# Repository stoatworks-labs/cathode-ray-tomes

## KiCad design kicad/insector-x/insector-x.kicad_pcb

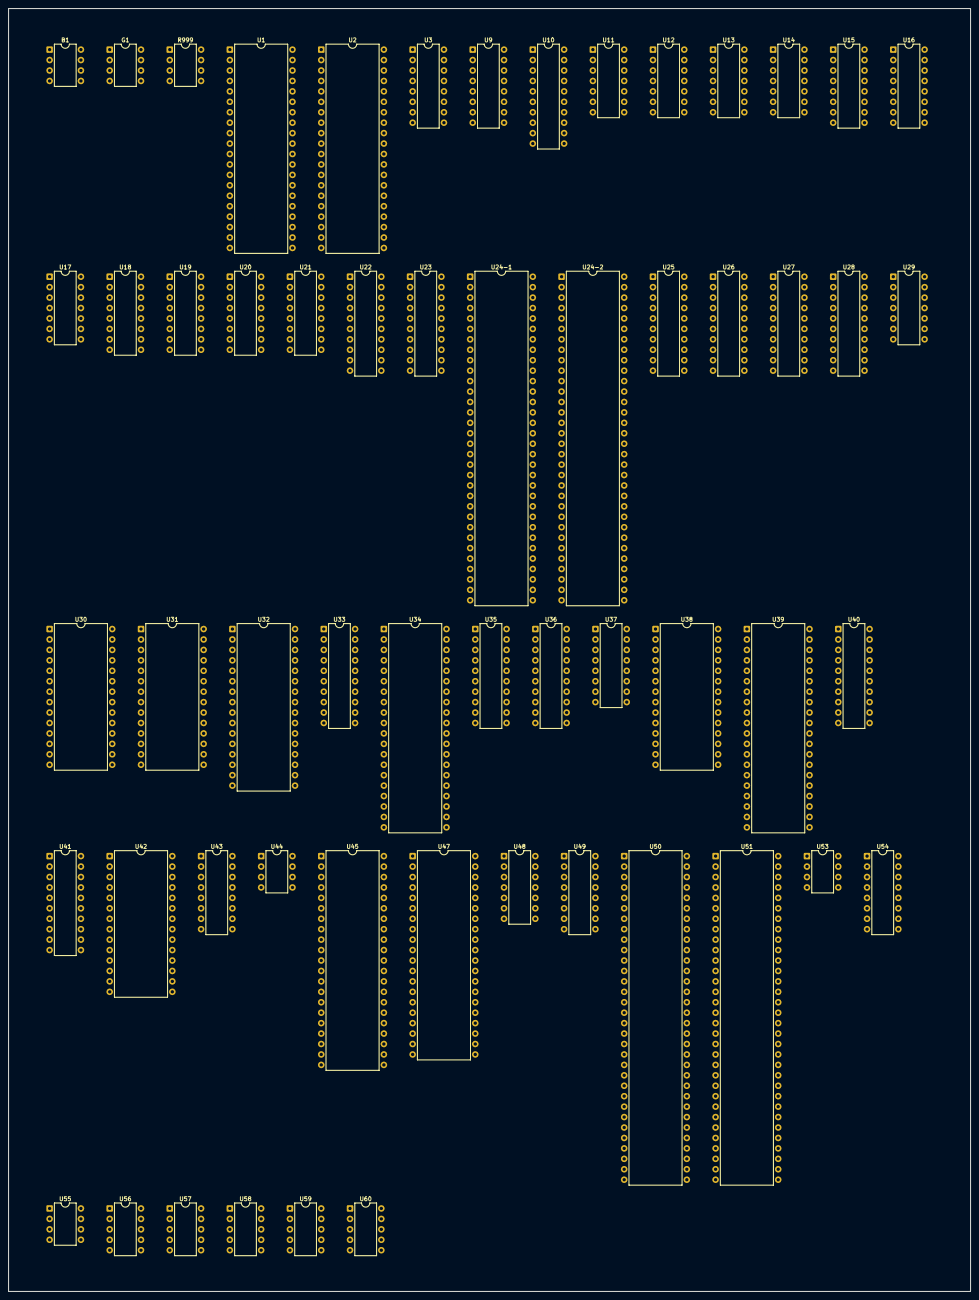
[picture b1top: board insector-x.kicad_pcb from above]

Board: 2 copper layers, 234.1 x 312.2 mm, 57 parts (0 on the bottom side), 330 nets, no tracks yet.

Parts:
B1: R0-012; DIP-8_W7.62mm
G1: R0-012; DIP-8_W7.62mm
R999: R0-012; DIP-8_W7.62mm
U1, U2: LH53400; DIP-40_W15.24mm
U3: 74LS139; DIP-16_W7.62mm
U9, U15, U37: 74LS174; DIP-16_W7.62mm
U10, U41: 74LS374; DIP-20_W7.62mm
U11: 74LS04; DIP-14_W7.62mm
U12: 74LS08; DIP-14_W7.62mm
U13, U14, U17: 74LS74; DIP-14_W7.62mm
U16, U18, U19, U20, U21: 74LS157; DIP-16_W7.62mm
U22: 74LS244_Split; DIP-20_W7.62mm
U23, U27, U28, U33, U40: 74LS245; DIP-20_W7.62mm
U24-1: YM3906; DIP-64_W15.24mm
U24-2: YM3909; DIP-64_W15.24mm
U25, U26, U35, U36: PAL16L8; DIP-20_W7.62mm
U29: 74LS32; DIP-14_W7.62mm
U30: HM6264; DIP-28_W15.24mm
U31: uPD43256BCZ-B; DIP-28_W15.24mm
U32: 27C010; DIP-32_W15.24mm
U34, U39: Z80CPU; DIP-40_W15.24mm
U38: 27512; DIP-28_W15.24mm
U42: TMM2063AP_10; DIP-28_W15.24mm
U43: TD62064; DIP-16_W7.62mm
U44: NJM4558; DIP-8_W7.62mm
U45: X1-007; DIP-42_W15.24mm
U47: YM2203; DIP-40_W15.24mm
U48: 74LS14; DIP-14_W7.62mm
U49, U54: 74LS161; DIP-16_W7.62mm
U50: X1-006; DIP-64_W15.24mm
U51: X1-004; DIP-64_W15.24mm
U53: YM3014; DIP-8_W7.62mm
U55: MB3730; DIP-8_W7.62mm
U56, U57, U58, U59, U60: X2-005; DIP-10_W7.62mm

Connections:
+12V: U43.1, U43.8, U55.7
/CPU/CNT_UP1: U37.5, U51.33
/CPU/CNT_UP2: U37.2, U51.32
/CPU/H2B: U12.4, U17.2, U22.18, U29.10, U47.38
/CPU/H4B: U12.5, U22.12, U23.19, U29.13, U33.19, U35.11
/CPU/MA0: U21.10, U23.8, U31.10, U32.12, U39.30, U50.34
/CPU/MA1: U21.13, U23.9, U31.9, U32.11, U39.31, U50.43
/CPU/MA2: U19.3, U23.7, U31.8, U32.10, U39.32, U50.42
/CPU/MA3: U20.13, U23.2, U31.7, U32.9, U39.33, U50.41
/CPU/MA4: U21.3, U23.4, U31.6, U32.8, U39.34, U50.40
/CPU/MA5: U21.6, U23.6, U31.5, U32.7, U39.35, U50.39
/CPU/MA6: U20.10, U31.4, U32.6, U33.4, U39.36, U50.38
/CPU/MA7: U20.6, U31.3, U32.5, U33.6, U39.37, U50.37
/CPU/MA8: U18.3, U31.25, U32.27, U33.7, U39.38, U50.36
/CPU/MA9: U18.6, U31.24, U32.26, U33.5, U36.7, U39.39, U50.35
/CPU/MA10: U19.10, U31.21, U32.23, U33.3, U36.6, U39.40
/CPU/MA11: U20.3, U24-1.27, U31.23, U32.25, U33.2, U36.5, U39.1
/CPU/MA12: U16.2, U19.13, U31.2, U32.4, U36.4, U39.2
/CPU/MA13: U31.1, U32.28, U36.3, U39.3
/CPU/MA14: U35.2, U36.2, U39.4
/CPU/MA15: U35.1, U36.1, U39.5
/CPU/MBSWD0: U15.2, U31.26, U35.7
/CPU/MBSWD1: U15.5, U35.6
/CPU/MBSWD2: U15.7, U35.5
/CPU/MCK6M: U14.11, U22.3, U22.15, U39.6
/CPU/MD0: U15.3, U28.9, U31.11, U32.13, U39.14, U40.3, U50.48, U50.56
/CPU/MD1: U15.4, U28.8, U31.12, U32.14, U39.15, U40.2, U50.49, U50.57
/CPU/MD2: U15.6, U28.7, U31.13, U32.15, U39.12, U40.9, U50.50, U50.58
/CPU/MD3: U15.14, U28.6, U31.15, U32.17, U39.8, U40.8, U50.51, U50.59
/CPU/MD4: U15.13, U28.5, U31.16, U32.18, U39.7, U40.7, U50.52, U50.60
/CPU/MD5: U15.11, U28.4, U31.17, U32.19, U39.9, U40.6, U50.53, U50.61
/CPU/MD6: U28.3, U31.18, U32.20, U39.10, U40.5, U50.54, U50.62
/CPU/MD7: U28.2, U31.19, U32.21, U39.13, U40.4, U50.55, U50.63
/CPU/MRA14: U32.29, U35.14
/CPU/MRA15: U32.3, U35.13
/CPU/MRA16: U32.2, U35.12
/CPU/SA0: U21.11, U34.30, U38.10, U47.37, U51.37
/CPU/SA1: U3.2, U21.14, U34.31, U38.9
/CPU/SA2: U3.3, U19.2, U34.32, U38.8
/CPU/SA3: U20.14, U34.33, U38.7
/CPU/SA4: U21.2, U34.34, U38.6
/CPU/SA5: U21.5, U34.35, U38.5
/CPU/SA6: U20.11, U34.36, U38.4
/CPU/SA7: U20.5, U34.37, U38.3
/CPU/SA8: U18.2, U34.38, U38.25
/CPU/SA9: U18.5, U34.39, U38.24
/CPU/SA10: U19.11, U34.40, U38.21
/CPU/SA11: U20.2, U25.5, U34.1, U38.23
/CPU/SA12: U19.14, U25.4, U34.2, U38.2
/CPU/SA13: U25.3, U34.3
/CPU/SA14: U25.2, U34.4
/CPU/SA15: U25.1, U34.5, U38.1
/CPU/SBANK0: U25.11, U37.15
/CPU/SBANK1: U25.9, U37.12
/CPU/SCK6M: U13.3, U13.11, U22.5, U34.6
/CPU/SD0: U27.9, U34.14, U37.14, U38.11, U47.40, U51.28, U51.44
/CPU/SD1: U27.8, U34.15, U37.13, U38.12, U47.2, U51.29, U51.45
/CPU/SD2: U27.7, U34.12, U37.11, U38.13, U47.3, U51.30, U51.46
/CPU/SD3: U27.6, U34.8, U37.6, U38.15, U47.4, U51.31, U51.47
/CPU/SD4: U27.5, U34.7, U37.4, U38.16, U47.5, U51.48
/CPU/SD5: U27.4, U34.9, U37.3, U38.17, U47.6, U51.49
/CPU/SD6: U27.3, U34.10, U38.18, U47.7, U51.50
/CPU/SD7: U27.2, U34.13, U38.19, U47.8, U51.51
/CPU/SET_LOCK1: U37.10, U51.35
/CPU/SET_LOCK2: U37.7, U51.34
/CPU/SHA0: U21.9, U30.10
/CPU/SHA1: U21.12, U30.9
/CPU/SHA2: U19.4, U30.8
/CPU/SHA3: U20.12, U30.7
/CPU/SHA4: U21.4, U30.6
/CPU/SHA5: U21.7, U30.5
/CPU/SHA6: U20.9, U30.4
/CPU/SHA7: U20.7, U30.3
/CPU/SHA8: U18.4, U30.25
/CPU/SHA9: U18.7, U30.24
/CPU/SHA10: U19.9, U30.21
/CPU/SHA11: U20.4, U30.23
/CPU/SHA12: U19.12, U30.2
/CPU/SHD0: U27.11, U28.11, U30.19
/CPU/SHD1: U27.12, U28.12, U30.18
/CPU/SHD2: U27.13, U28.13, U30.17
/CPU/SHD3: U27.14, U28.14, U30.16
/CPU/SHD4: U27.15, U28.15, U30.15
/CPU/SHD5: U27.16, U28.16, U30.13
/CPU/SHD6: U27.17, U28.17, U30.12
/CPU/SHD7: U27.18, U28.18, U30.11
/CPU/SRA13: U25.18, U38.26
/CPU/SRA14: U25.19, U38.27
/CPU/~BGTRNSP: U24-2.2, U36.14
/CPU/~BNKSW: U15.9, U36.15
/CPU/~MIORQ: U14.1, U39.20
/CPU/~MMREQ: U35.3, U36.8, U39.19
/CPU/~MRAMCS: U31.20, U35.16
/CPU/~MRD: U11.9, U18.10, U24-1.2, U28.1, U31.22, U39.21, U40.1, U50.44
/CPU/~MRFSH: U35.4, U36.9, U39.28
/CPU/~MROMCS: U32.24, U35.15
/CPU/~MSHRAMEN: U26.16, U28.19
/CPU/~MSHRAMRQ: U26.1, U36.18
/CPU/~MWAIT: U26.14, U39.24
/CPU/~MWR: U26.2, U31.27, U36.11, U39.22, U50.47
/CPU/~OBJCODEHI: U35.9, U36.17
/CPU/~OBJCODELO: U35.8, U36.16
/CPU/~OBJORVRAMEN: U26.5, U29.12, U36.19
/CPU/~OBJRAMCS: U35.19, U42.20
/CPU/~PALEN: U36.12, U50.45
/CPU/~RDINPUTS: U3.1, U25.16
/CPU/~SBNKSW: U25.14, U37.9
/CPU/~SHRAMCS: U26.17, U30.20
/CPU/~SHRAMRD: U18.9, U30.22
/CPU/~SHRAMWR: U26.18, U30.27
/CPU/~SIORQ: U17.13, U34.20
/CPU/~SMREQ: U25.7, U34.19
/CPU/~SRD: U18.11, U27.1, U34.21, U47.36
/CPU/~SRFSH: U25.8, U34.28
/CPU/~SROMCS: U25.12, U38.22
/CPU/~SRST: U12.3, U34.26, U37.1, U47.24
/CPU/~SSHRAMENB: U18.1, U19.1, U20.1, U21.1, U26.19
/CPU/~SSHRAMEN: U26.15, U27.19
/CPU/~SSHRAMRQ: U25.13, U26.3
/CPU/~SWAIT: U26.13, U34.24
/CPU/~SWR: U25.6, U26.4, U34.22, U47.35
/CPU/~VRAMWR: U24-1.3, U36.13
/CPU/~WDRES: U12.1, U15.1, U24-1.29, U39.26, U48.2, U48.4
/CPU/~YM2203CS: U13.2, U25.15, U47.34
/CPU/~YMIRQ: U34.17, U47.25
/Graphics/12M: U24-1.62, U24-2.3
/Graphics/B1: B1.3, U45.2
/Graphics/B2: B1.4, U45.3
/Graphics/B3: B1.5, U45.4
/Graphics/B4: B1.6, U45.5
/Graphics/B5: B1.7, U45.6
/Graphics/Bb: B1.2, U45.1
/Graphics/G1: G1.3, U45.8
/Graphics/G2: G1.4, U45.9
/Graphics/G2D0: U2.13, U24-2.56
/Graphics/G2D1: U2.15, U24-2.57
/Graphics/G2D2: U2.17, U24-2.58
/Graphics/G2D3: U2.19, U24-2.59
/Graphics/G2D4: U2.22, U24-2.60
/Graphics/G2D5: U2.24, U24-2.61
/Graphics/G2D6: U2.26, U24-2.62
/Graphics/G2D7: U2.28, U24-2.63
/Graphics/G2D8: U2.14, U24-2.48
/Graphics/G2D9: U2.16, U24-2.49
/Graphics/G2D10: U2.18, U24-2.50
/Graphics/G2D11: U2.20, U24-2.51
/Graphics/G2D12: U2.23, U24-2.52
/Graphics/G2D13: U2.25, U24-2.53
/Graphics/G2D14: U2.27, U24-2.54
/Graphics/G2D15: U2.29, U24-2.55
/Graphics/G3: G1.5, U45.11
/Graphics/G4: G1.6, U45.12
/Graphics/G5: G1.7, U45.13
/Graphics/GA0: U1.9, U2.9, U24-1.38
/Graphics/GA1: U1.8, U2.8, U24-1.37
/Graphics/GA2: U1.7, U2.7, U24-1.36
/Graphics/GA4: U1.5, U2.5, U24-1.35
/Graphics/GA5: U1.4, U2.4, U10.15
/Graphics/GA6: U1.3, U2.3, U10.16
/Graphics/GA7: U1.2, U2.2, U10.2
/Graphics/GA8: U1.40, U2.40, U10.5
/Graphics/GA9: U1.39, U2.39, U10.6
/Graphics/GA10: U1.38, U2.38, U10.9
/Graphics/GA11: U1.37, U2.37, U10.12
/Graphics/GA12: U1.36, U2.36, U10.19
/Graphics/GA13: U1.35, U2.35, U9.5
/Graphics/GA14: U1.34, U2.34, U9.2
/Graphics/GA15: U1.33, U2.33, U9.12
/Graphics/GA16: U1.32, U2.32, U9.15
/Graphics/GA17: U1.1, U2.1, U9.10
/Graphics/GD0: U1.13, U24-2.40
/Graphics/GD1: U1.15, U24-2.41
/Graphics/GD2: U1.17, U24-2.42
/Graphics/GD3: U1.19, U24-2.43
/Graphics/GD4: U1.22, U24-2.44
/Graphics/GD5: U1.24, U24-2.45
/Graphics/GD6: U1.26, U24-2.46
/Graphics/GD7: U1.28, U24-2.47
/Graphics/GD8: U1.14, U24-2.30
/Graphics/GD9: U1.16, U24-2.31
/Graphics/GD10: U1.18, U24-2.34
/Graphics/GD11: U1.20, U24-2.35
/Graphics/GD12: U1.23, U24-2.36
/Graphics/GD13: U1.25, U24-2.37
/Graphics/GD14: U1.27, U24-2.38
/Graphics/GD15: U1.29, U24-2.39
/Graphics/Gb: G1.2, U45.7
/Graphics/H: U22.6, U24-1.40
/Graphics/H2: U22.2, U24-1.41
/Graphics/H2SYNC: U11.11, U29.8, U41.11
/Graphics/H4: U11.1, U16.1, U22.8, U24-1.42
/Graphics/H8: U9.9, U10.11, U24-1.43, U54.2
/Graphics/H8R: U1.6, U2.6, U24-1.34
/Graphics/HX: U22.13, U24-1.39
/Graphics/MAB11: U24-1.26, U33.18
/Graphics/OBJRD: U24-1.30, U29.5
/Graphics/R1: R999.3, U45.15
/Graphics/R2: R999.4, U45.16
/Graphics/R3: R999.5, U45.17
/Graphics/R4: R999.6, U45.18
/Graphics/R5: R999.7, U45.19
/Graphics/Rb: R999.2, U45.14
/Graphics/VA0: U23.12, U24-1.15, U42.10
/Graphics/VA1: U23.11, U24-1.16, U42.9
/Graphics/VA2: U23.13, U24-1.17, U42.8
/Graphics/VA3: U23.18, U24-1.18, U42.7
/Graphics/VA4: U23.16, U24-1.19, U42.6
/Graphics/VA5: U23.14, U24-1.20, U42.5
/Graphics/VA6: U24-1.21, U33.16, U42.4
/Graphics/VA7: U24-1.22, U33.14, U42.3
/Graphics/VA8: U24-1.23, U33.13, U42.25
/Graphics/VA9: U24-1.24, U33.15, U42.24
/Graphics/VA10: U24-1.25, U33.17, U42.21
/Graphics/VA11: U24-1.28, U42.23
/Graphics/VA12: U16.4, U42.2
/Graphics/VD0: U10.14, U24-1.14, U40.17, U41.18, U42.11
/Graphics/VD1: U10.17, U24-1.13, U40.18, U41.3, U42.12
/Graphics/VD2: U10.3, U24-1.12, U40.11, U41.8, U42.13
/Graphics/VD3: U10.4, U24-1.11, U40.12, U41.13, U42.15
/Graphics/VD4: U10.7, U24-1.10, U40.13, U41.7, U42.16
/Graphics/VD5: U10.8, U24-1.9, U40.14, U41.14, U42.17
/Graphics/VD6: U10.13, U24-1.8, U33.9, U40.15, U41.4, U42.18
/Graphics/VD7: U10.18, U24-1.7, U33.8, U40.16, U41.17, U42.19
/Graphics/VDB0: U9.4, U24-1.4, U41.19
/Graphics/VDB1: U9.3, U41.2
/Graphics/VDB2: U9.13, U23.17, U24-2.10, U41.9
/Graphics/VDB3: U9.14, U24-2.9, U41.12
/Graphics/VDB4: U9.11, U24-2.8, U41.6
/Graphics/VDB5: U9.6, U24-2.7, U41.15
/Graphics/VDB6: U24-1.59, U24-2.6, U33.11, U41.5
/Graphics/VDB7: U24-1.60, U24-2.5, U33.12, U41.16
/Graphics/~HBLK: U24-1.55, U48.5
/Graphics/~HSYNC: U45.22, U54.12
/Graphics/~VBLK: U11.13, U24-1.58, U45.24
/Graphics/~VSYNC: U24-1.56, U45.23
/IO/1P_BTN_1_B: U51.5, U56.6
/IO/1P_BTN_2_B: U51.4, U57.10
/IO/1P_BTN_3_B: U51.3, U57.8
/IO/1P_DOWN_B: U51.6, U58.4
/IO/1P_LEFT_B: U51.9, U58.10
/IO/1P_RIGHT_B: U51.8, U58.8
/IO/1P_START_B: U51.2, U56.4
/IO/1P_UP_B: U51.7, U58.6
/IO/2P_BTN_1_B: U51.13, U56.10
/IO/2P_BTN_2_B: U51.12, U59.6
/IO/2P_BTN_3_B: U51.11, U59.4
/IO/2P_DOWN_B: U51.14, U59.8
/IO/2P_LEFT_B: U51.17, U60.6
/IO/2P_RIGHT_B: U51.16, U60.4
/IO/2P_START_B: U51.10, U56.8
/IO/2P_UP_B: U51.15, U59.10
/IO/COIN_1_B: U51.22, U60.10
/IO/COIN_2_B: U51.23, U60.8
/IO/COIN_CNT_1_A: U43.6, U51.20
/IO/COIN_CNT_2_A: U43.3, U51.21
/IO/COIN_LOCK_1_A: U43.14, U51.18
/IO/COIN_LOCK_2_A: U43.11, U51.19
/IO/SERVICE_B: U51.25, U57.4
/IO/TILT_B: U51.24, U57.6
GND: B1.8, G1.8, R999.8, U1.10, U1.11, U1.12, U1.30, U2.10, U2.11, U2.12, U2.30, U9.8, U10.1, U10.10, U16.6, U16.15, U18.15, U19.15, U20.15, U21.15, U22.1, U22.19, U23.3, U23.5, U24-1.31, U24-1.32, U24-1.45, U24-1.64, U24-2.32, U24-2.64, U25.10, U26.10, U31.14, U32.16, U32.22, U34.29, U35.10, U36.10, U38.14, U38.20, U39.29, U42.22, U43.4, U43.5, U43.12, U43.13, U44.4, U45.21, U45.26, U47.1, U49.3, U49.4, U49.5, U49.6, U50.19, U50.20, U50.33, U50.46, U51.1, U51.26, U51.36, U51.38, U51.39, U51.42, U54.8, U55.4, U56.1, U57.1, U58.1, U59.1, U60.1
unnamed: U12.2, U15.12
unnamed: U11.3, U22.7
unnamed: U48.8, U48.11
unnamed: U12.9, U48.13
unnamed: U3.4, U51.41
unnamed: U3.5, U51.40
unnamed: U11.8, U29.4
unnamed: U13.5, U13.12
unnamed: U13.6, U26.11
unnamed: U13.4, U13.9, U26.9
unnamed: U11.12, U14.3, U17.11
unnamed: U14.6, U39.16
unnamed: U12.6, U14.12
unnamed: U14.9, U26.6
unnamed: U11.10, U16.3
unnamed: U11.5, U17.3, U22.4, U22.14
unnamed: U17.6, U29.9
unnamed: U17.8, U34.16
unnamed: U24-1.61, U24-2.4
unnamed: U24-1.46, U24-2.19
unnamed: U24-1.47, U24-2.18
unnamed: U24-1.48, U24-2.17
unnamed: U24-1.49, U24-2.16
unnamed: U24-1.50, U24-2.15
unnamed: U24-1.51, U24-2.14
unnamed: U24-1.52, U24-2.13
unnamed: U24-1.53, U24-2.12
unnamed: U24-1.54, U24-2.11
unnamed: U24-2.20, U50.23
unnamed: U24-2.21, U50.24
unnamed: U24-2.22, U50.25
unnamed: U24-2.23, U50.26
unnamed: U24-2.24, U50.27
unnamed: U24-2.25, U50.28
unnamed: U24-2.26, U50.29
unnamed: U24-2.27, U50.30
unnamed: U24-2.28, U50.31
unnamed: U29.2, U48.12
unnamed: U29.3, U48.1, U48.3
unnamed: U29.11, U40.19
unnamed: U11.2, U41.1
unnamed: U29.6, U42.27
unnamed: U44.3, U53.2
unnamed: U44.1, U44.2
unnamed: U44.5, U53.7
unnamed: U44.6, U44.7, U53.8
unnamed: U45.41, U50.1
unnamed: U45.40, U50.2
unnamed: U45.39, U50.3
unnamed: U45.38, U50.4
unnamed: U45.37, U50.5
unnamed: U45.36, U50.6
unnamed: U45.35, U50.7
unnamed: U45.34, U50.8
unnamed: U45.33, U50.9
unnamed: U45.32, U50.10
unnamed: U45.31, U50.11
unnamed: U45.30, U50.12
unnamed: U45.29, U50.13
unnamed: U45.28, U50.14
unnamed: U45.27, U50.15
unnamed: U47.18, U47.19, U47.20
unnamed: U47.23, U53.4
unnamed: U47.39, U53.5
unnamed: U47.22, U53.3
unnamed: U48.10, U49.2
unnamed: U29.1, U49.11
unnamed: U12.8, U49.1
unnamed: U48.6, U54.9
VCC: U1.21, U1.31, U2.21, U2.31, U9.1, U9.16, U10.20, U13.1, U13.10, U13.13, U14.2, U14.4, U14.10, U14.13, U16.10, U17.1, U17.4, U17.10, U17.12, U23.1, U24-1.1, U24-1.33, U24-2.1, U24-2.33, U25.20, U26.20, U30.26, U31.28, U32.1, U32.31, U32.32, U33.1, U34.11, U34.25, U35.20, U36.20, U38.28, U39.11, U39.17, U39.25, U42.26, U44.8, U45.42, U47.21, U49.7, U49.10, U50.17, U50.18, U50.21, U50.22, U50.64, U51.27, U51.43, U51.52, U53.1, U54.1, U54.3, U54.4, U54.5, U54.6, U54.7, U54.10, U54.16, U56.2, U57.2, U58.2, U59.2, U60.2

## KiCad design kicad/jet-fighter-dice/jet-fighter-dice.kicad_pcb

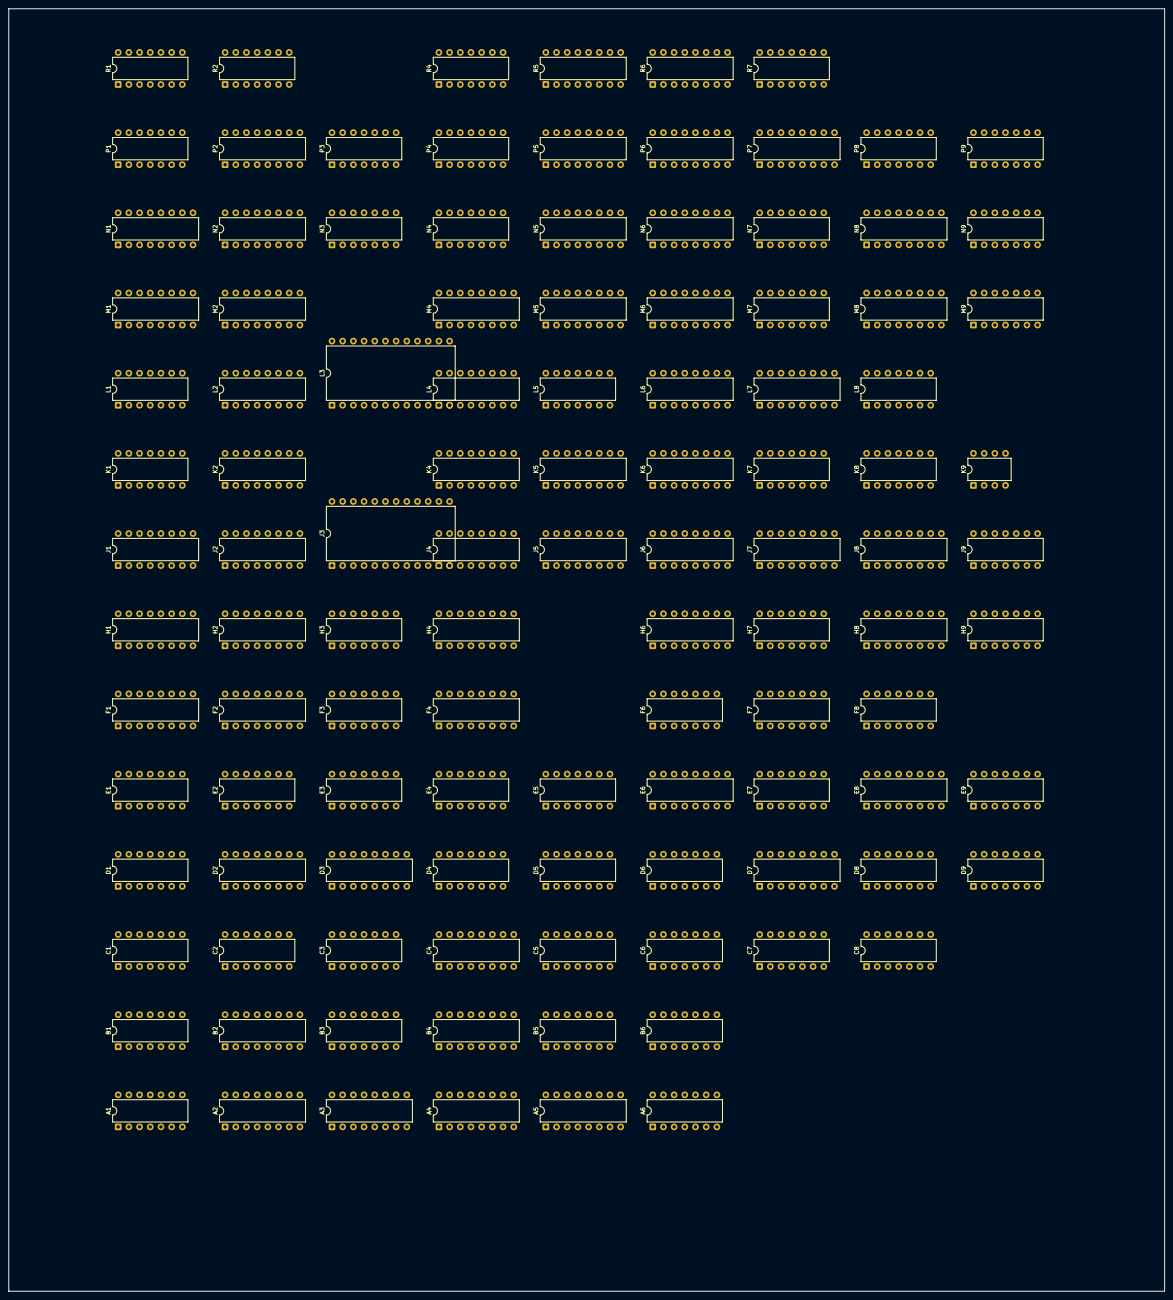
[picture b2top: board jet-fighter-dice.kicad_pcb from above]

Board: 2 copper layers, 274.6 x 304.7 mm, 110 parts (0 on the bottom side), 401 nets, no tracks yet.

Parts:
A1: 7486; DIP-14_W7.62mm
A2: 9316; DIP-16_W7.62mm
A3: 74153; DIP-16_W7.62mm
A4: 74S287; DIP-16_W7.62mm
A5: 9322; DIP-16_W7.62mm
A6: 7493; DIP-14_W7.62mm
B1: 74164; DIP-14_W7.62mm
B2, B4: 9316; DIP-16_W7.62mm
B3, B6: 7474; DIP-14_W7.62mm
B5: 7493; DIP-14_W7.62mm
C1, C3: 7400; DIP-14_W7.62mm
C2, C7: 7404; DIP-14_W7.62mm
C4: 9316; DIP-16_W7.62mm
C5: 7427; DIP-14_W7.62mm
C6: 7420; DIP-14_W7.62mm
C8: 7474; DIP-14_W7.62mm
D1: 7432; DIP-14_W7.62mm
D2, D3: 74175; DIP-16_W7.62mm
D4, D8: 7400; DIP-14_W7.62mm
D5: 7490; DIP-14_W7.62mm
D6: 7402; DIP-14_W7.62mm
D7: 9316; DIP-16_W7.62mm
D9: 7413; DIP-14_W7.62mm
E1, E5: 7410; DIP-14_W7.62mm
E2: 7420; DIP-14_W7.62mm
E3: 7437; DIP-14_W7.62mm
E4: 7408; DIP-14_W7.62mm
E6: 9316; DIP-16_W7.62mm
E7: 7474; DIP-14_W7.62mm
E8: 74279; DIP-16_W7.62mm
E9: 7413; DIP-14_W7.62mm
F1: 74175; DIP-16_W7.62mm
F2: 9316; DIP-16_W7.62mm
F3: 7410; DIP-14_W7.62mm
F4: 74165; DIP-16_W7.62mm
F6: 7474; DIP-14_W7.62mm
F7: 7400; DIP-14_W7.62mm
F8: 7404; DIP-14_W7.62mm
H1: 9312; DIP-16_W7.62mm
H2: 9316; DIP-16_W7.62mm
H3, H7: 7408; DIP-14_W7.62mm
H4: 74165; DIP-16_W7.62mm
H6: 74193; DIP-16_W7.62mm
H8: 74153; DIP-16_W7.62mm
H9: 7414; DIP-14_W7.62mm
J1: 82S123; DIP-16_W7.62mm
J2: 9316; DIP-16_W7.62mm
J3: 74116; DIP-24_W15.24mm
J4: 74165; DIP-16_W7.62mm
J5: 82S131; DIP-16_W7.62mm
J6, J8: 9322; DIP-16_W7.62mm
J7: 74193; DIP-16_W7.62mm
J9: 7414; DIP-14_W7.62mm
K1: 7400; DIP-14_W7.62mm
K2: 9316; DIP-16_W7.62mm
K4: 74165; DIP-16_W7.62mm
K5: 82S131; DIP-16_W7.62mm
K6: 9322; DIP-16_W7.62mm
K7: 7486; DIP-14_W7.62mm
K8: 7432; DIP-14_W7.62mm
K9: 555; DIP-8_W7.62mm
L1, L5: 7400; DIP-14_W7.62mm
L2, L6, L7: 9316; DIP-16_W7.62mm
L3: 74116; DIP-24_W15.24mm
L4: 74153; DIP-16_W7.62mm
L8: 7404; DIP-14_W7.62mm
M1: 82S123; DIP-16_W7.62mm
M2, M5, M6: 9316; DIP-16_W7.62mm
M4: 74153; DIP-16_W7.62mm
M7: 7404; DIP-14_W7.62mm
M8: 8225; DIP-16_W7.62mm
M9: 7493; DIP-14_W7.62mm
N1: 9312; DIP-16_W7.62mm
N2, N5, N6: 9316; DIP-16_W7.62mm
N3, N7: 7408; DIP-14_W7.62mm
N4: 7474; DIP-14_W7.62mm
N8: 8225; DIP-16_W7.62mm
N9: 7493; DIP-14_W7.62mm
P1, P4, P9: 7474; DIP-14_W7.62mm
P2, P6, P7: 9316; DIP-16_W7.62mm
P3: 7492; DIP-14_W7.62mm
P5: 74175; DIP-16_W7.62mm
P8: 7400; DIP-14_W7.62mm
R1: 74H04; DIP-14_W7.62mm
R2: 7410; DIP-14_W7.62mm
R4: 7474; DIP-14_W7.62mm
R5: 82S123; DIP-16_W7.62mm
R6: 74153; DIP-16_W7.62mm
R7: 7402; DIP-14_W7.62mm

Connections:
+5V: A1.14, A2.16, A3.16, A5.16, A6.5, B1.14, B2.16, B3.14, B4.16, B5.5, B6.14, C1.14, C2.14, C3.14, C4.16, C5.14, C6.14, C7.14, C8.14, D1.14, D2.16, D3.16, D4.14, D5.5, D6.14, D7.16, D8.14, D9.14, E1.14, E2.14, E3.14, E4.14, E5.14, E6.16, E7.14, E8.16, E9.14, F1.16, F2.16, F3.14, F4.16, F6.14, F7.14, F8.14, H1.16, H2.16, H3.14, H4.16, H6.16, H7.14, H8.16, H9.14, J1.16, J2.16, J4.16, J6.16, J7.16, J8.16, J9.14, K1.14, K2.16, K4.16, K6.16, K7.14, K8.14, K9.8, L1.14, L2.16, L4.16, L5.14, L6.16, L7.16, L8.14, M1.16, M2.16, M4.16, M5.16, M6.16, M7.14, M9.5, N1.16, N2.16, N3.14, N4.14, N5.16, N6.16, N7.14, N9.5, P1.14, P2.16, P3.5, P4.14, P5.16, P6.16, P7.16, P8.14, P9.14, R1.14, R2.14, R4.14, R5.16, R6.16, R7.14
A1-3: A1.3, C6.10
A1-5: A1.5, D3.3
A1-6: A1.6, C1.10, C1.13
A1-8: A1.8, C1.2, C1.5
A1-9: A1.9, D3.6
A2-15: A2.15, B2.7, B2.10
A3-3: A3.3, C3.6
A3-7: A3.7, B1.1, B1.2
A3-9: A3.9, F1.12
A3-10: A3.10, A4.12
A3-11: A3.11, A4.11
A3-12: A3.12, A4.10
A3-13: A3.13, A4.9
A3-15: A3.15, C6.8
A4-1: A4.1, A5.7
A4-2: A4.2, A5.12
A4-3: A4.3, A5.9
A4-15: A4.15, A5.4
B1-4: B1.4, C1.12
B1-6: B1.6, C1.9
B1-11: B1.11, C1.4
B1-13: B1.13, C1.1
B2-9: B2.9, C2.10
B2-15: B2.15, C2.11
B4-15: B4.15, C4.7, C4.10
C2-2: C2.2, J2.5
C2-13: C2.13, C4.15
C3-1: C3.1, C3.13, F1.10
C3-5: C3.5, E1.12
C5-4: C5.4, D4.12, P9.5
C5-8: C5.8, C6.9
C6-6: C6.6, C7.3
C6-12: C6.12, E4.8
C7-4: C7.4, F7.2, F7.4, F7.10, F7.12
C7-12: C7.12, D4.9
C7-13: C7.13, D5.1, D5.12
C8-4: C8.4, D8.4
C8-8: C8.8, C8.12
D1-3: D1.3, L3.2, L3.14
D1-6: D1.6, L8.1, N8.3
D1-8: D1.8, J3.2, J3.14
D1-11: D1.11, L8.13, M8.3
D2-4: D2.4, L5.12, L6.15
D2-5: D2.5, L5.10, P6.15
D3-11: D3.11, D3.12
D3-13: D3.13, D8.3
D4-1: D4.1, F3.12
D4-6: D4.6, F4.15, H4.15
D4-8: D4.8, E8.1
D5-8: D5.8, E5.9
D5-9: D5.9, E5.10
D5-14: D5.14, J9.6
D6-2: D6.2, E6.12
D6-3: D6.3, E6.13
D6-4: D6.4, N4.3, N4.11
D6-10: D6.10, P4.3, P4.11
D6-11: D6.11, D7.13
D6-12: D6.12, D7.12
D7-9: D7.9, E4.3
D7-11: D7.11, D8.9
D8-1: D8.1, D9.8, E8.14
D8-2: D8.2, D9.6
D8-13: D8.13, E6.11
E1-6: E1.6, E7.1
E1-8: E1.8, E7.13
E2-1: E2.1, R4.9
E2-2: E2.2, K7.11
E2-9: E2.9, K7.3
E2-13: E2.13, R4.5
E4-1: E4.1, E5.6
E4-5: E4.5, F3.8
E4-11: E4.11, E6.9
E4-13: E4.13, E5.12
F1-4: F1.4, N1.14
F1-5: F1.5, H1.14
F1-13: F1.13, F1.14
F2-1: F2.1, H2.1, J2.1, K2.1, P1.9
F2-7: F2.7, H2.15, K1.5
F2-10: F2.10, H2.11
F2-15: F2.15, F3.5, K1.4
F3-4: F3.4, K1.13, K2.15
F3-6: F3.6, H1.10
F4-9: F4.9, H4.10
F6-3: F6.3, H7.8
F6-11: F6.11, H7.11
F7-3: F7.3, H7.2
F7-6: F7.6, J7.4
F7-8: F7.8, H6.4
F7-11: F7.11, H7.5
F8-3: F8.3, P9.1, P9.12, P9.13
GND: A1.7, A2.3, A2.4, A2.5, A2.6, A2.8, A3.4, A3.5, A3.6, A3.8, A4.13, A4.14, A5.8, A5.15, A6.10, B1.7, B2.3, B2.4, B2.6, B2.8, B3.7, B4.3, B4.4, B4.5, B4.8, B5.10, B6.7, C1.7, C2.7, C3.7, C4.6, C4.8, C5.3, C5.5, C5.7, C6.7, C7.7, C8.7, D1.7, D2.8, D3.8, D4.7, D5.10, D6.7, D7.3, D7.4, D7.5, D7.8, D8.7, D9.7, E1.7, E2.7, E3.7, E4.7, E5.7, E6.3, E6.4, E6.5, E6.8, E7.7, E8.8, E9.7, F1.8, F2.3, F2.4, F2.5, F2.6, F2.8, F3.7, F4.8, F4.10, F6.7, F7.7, F8.7, H1.8, H2.8, H3.7, H4.8, H6.1, H6.8, H6.9, H6.10, H6.15, H7.7, H8.3, H8.5, H8.8, H8.11, H8.13, H9.7, J1.8, J2.8, J4.8, J4.10, J5.13, J6.8, J6.15, J7.1, J7.8, J7.9, J7.10, J7.15, J8.8, J8.15, J9.7, K1.7, K2.3, K2.4, K2.5, K2.6, K2.8, K4.8, K5.13, K6.8, K6.15, K7.7, K8.7, K9.1, L1.7, L2.3, L2.4, L2.5, L2.6, L2.8, L4.8, L5.7, L6.3, L6.4, L6.6, L6.8, L7.6, L7.8, L8.7, M1.8, M2.8, M4.8, M5.3, M5.4, M5.5, M5.6, M5.8, M6.6, M6.8, M7.7, M8.2, M9.2, M9.3, M9.10, N1.8, N2.8, N3.7, N4.7, N5.3, N5.4, N5.5, N5.6, N5.8, N6.6, N6.8, N7.7, N8.2, N9.2, N9.3, N9.10, P1.7, P2.3, P2.4, P2.5, P2.6, P2.8, P3.6, P3.7, P3.10, P4.7, P5.8, P6.3, P6.4, P6.8, P7.6, P7.8, P8.7, P9.7, R1.7, R2.7, R4.7, R5.8, R6.1, R6.8, R6.15, R7.7
H1-1: H1.1, J1.1
H1-2: H1.2, J1.2
H1-3: H1.3, J1.3
H1-4: H1.4, J1.4
H1-5: H1.5, J1.5
H1-6: H1.6, J1.6
H1-7: H1.7, J1.7
H1-9: H1.9, J1.9
H2-3: H2.3, H3.3
H2-4: H2.4, H3.11
H2-5: H2.5, K1.8
H2-6: H2.6, H3.8
H2-9: H2.9, K1.6
H3-6: H3.6, J3.1, J3.13
H4-7: H4.7, K7.12
H6-5: H6.5, H7.6
H6-12: H6.12, H7.10
H6-13: H6.13, H7.9
H7-1: H7.1, K8.3
H7-3: H7.3, J7.5
H7-4: H7.4, K8.11
H7-12: H7.12, J7.12
H7-13: H7.13, J7.13
J2-9: J2.9, K1.11
J2-11: J2.11, K2.10
J2-15: J2.15, K1.12, K2.7
J4-9: J4.9, K4.10
J4-15: J4.15, K4.15, L1.8
J9-5: J9.5, K9.3
K4-7: K4.7, K7.1
K7-2: K7.2, K8.6
K7-6: K7.6, P8.5
K7-8: K7.8, P8.10
K7-13: K7.13, K8.8
L1-1: L1.1, L2.7, M2.15
L1-2: L1.2, L2.15, R2.1
L1-3: L1.3, M2.9
L1-4: L1.4, P2.15, R2.2
L1-5: L1.5, N2.15, P2.7
L1-6: L1.6, N2.9
L1-11: L1.11, N2.5
L2-1: L2.1, M2.1, N2.1, P1.5, P2.1
L2-10: L2.10, M2.11
L3-1: L3.1, L3.13, N3.8
L4-2: L4.2, P4.9
L4-7: L4.7, L8.11, P8.9
L4-9: L4.9, L8.9, P8.13
L4-14: L4.14, P4.6
L5-1: L5.1, M5.15, R4.1
L5-2: L5.2, M5.7, M6.15
L5-4: L5.4, N5.15, R4.13
L5-5: L5.5, N5.7, N6.15
L5-8: L5.8, P7.9
L5-9: L5.9, P6.7, P7.15
L5-11: L5.11, L7.9
L5-13: L5.13, L6.7, L7.15
L6-10: L6.10, L7.11
L7-3: L7.3, N7.11
L7-4: L7.4, M7.5, N7.8
L7-5: L7.5, M7.6
L8-3: L8.3, M4.7, P8.4
L8-4: L8.4, N8.12
L8-5: L8.5, M4.9, P8.2
L8-6: L8.6, N8.6
L8-8: L8.8, M8.6
L8-10: L8.10, M8.12
L8-12: L8.12, M9.14
M1-1: M1.1, N1.1
M1-2: M1.2, N1.2
M1-3: M1.3, N1.3
M1-4: M1.4, N1.4
M1-5: M1.5, N1.5
M1-6: M1.6, N1.6
M1-7: M1.7, N1.7
M1-9: M1.9, N1.9
M2-5: M2.5, R1.8
M4-2: M4.2, N4.9
M4-14: M4.14, N4.6
M5-10: M5.10, M6.11
M6-5: M6.5, M7.8
M7-2: M7.2, N6.5
M7-3: M7.3, N7.6, P7.4
M7-4: M7.4, P7.5
M7-10: M7.10, R7.9
M7-11: M7.11, R6.9, R7.5, R7.11
M7-12: M7.12, R7.12
M7-13: M7.13, R6.7, R7.6, R7.8
M8-1: M8.1, M9.1, M9.12
M8-4: M8.4, P8.11
M8-10: M8.10, P8.8
M8-13: M8.13, M9.11
M8-14: M8.14, M9.8
M8-15: M8.15, M9.9
N1-10: N1.10, R2.12
N2-3: N2.3, N3.6
N2-4: N2.4, N3.3
N2-6: N2.6, N3.11
N2-11: N2.11, P2.10
N4-2: N4.2, N4.8
N4-5: N4.5, N4.12
N5-10: N5.10, N6.11
N7-3: N7.3, P7.3
N8-1: N8.1, N9.1, N9.12
N8-4: N8.4, P8.3
N8-10: N8.10, P8.6
N8-13: N8.13, N9.11
N8-14: N8.14, N9.8
N8-15: N8.15, N9.9
P1-3: P1.3, R1.12
P1-11: P1.11, R1.10
P4-2: P4.2, P4.8
P4-5: P4.5, P4.12
P5-2: P5.2, R5.13
P5-7: P5.7, R5.14
P5-10: P5.10, R5.11
P5-15: P5.15, R5.12
P6-10: P6.10, P7.11
P9-2: P9.2, P9.9
R1-11: R1.11, R2.8
R1-13: R1.13, R2.6
R5-1: R5.1, R6.6
R5-2: R5.2, R6.5
R5-3: R5.3, R6.4
R5-4: R5.4, R6.3
R5-5: R5.5, R6.10
R5-6: R5.6, R6.11
R5-7: R5.7, R6.12
R5-9: R5.9, R6.13
VCC: A2.1, A2.9, B1.9, B2.1, B2.5, B3.4, B3.13, B4.1, B4.6, B6.2, B6.4, B6.10, C4.1, C4.3, C4.4, C4.5, C8.1, C8.10, C8.13, D2.1, D3.1, D4.2, D7.1, D7.10, E4.4, E6.1, E6.10, E7.2, E7.4, E7.10, E7.12, E8.3, F1.1, F2.9, F6.4, F6.10, H2.7, H2.10, H6.11, J2.7, J2.10, J7.11, K2.9, L2.9, L6.1, L6.5, L7.7, L7.10, M2.7, M2.10, M5.1, M5.9, M6.1, N2.7, N2.10, N4.1, N4.4, N4.10, N4.13, N5.1, N5.9, N6.1, P1.2, P1.4, P1.10, P1.12, P2.9, P4.1, P4.4, P4.10, P4.13, P5.1, P6.1, P6.5, P6.6, P7.7, P7.10, P9.4, P9.10, R4.4, R4.10
_1CREDIT: D8.6, D9.5
_1F: C6.5, C8.9, H8.14, K8.1, K8.13, P3.1, P3.14
_1H: A2.7, A2.10, F1.15
_1PLAY: E8.13, J8.1
_1V: B4.7, B4.10, D3.10
_2CREDIT: C8.5, D8.5, D9.9
_2F: H8.2, P3.12
_2V: A4.6, B4.14, B6.3
_3F: C6.4, D7.2, E6.2, E7.3, E7.11, J1.13, K8.5, K8.9, M1.13, P3.9
_4H: A2.13, A4.5, B1.8, B3.3
_4V: A4.7, B4.13, B6.11
_6F: E5.11, P3.8
_8H: A2.12, A3.14
_8V: A4.4, B4.12
_12MHZ: D2.9, F4.2, H4.2, J4.2, K4.2
_16H: A2.11, A3.2, J5.5, K5.5
_16V: B4.11, E4.9
_32H: A1.1, B2.14, B3.11, C3.12, E1.2, J6.1, K6.1
_32V: C4.14, C5.9
_64H: B2.13, C2.3, E1.1
_64Hn: A1.13, B3.10, C2.4
_64Hxnor128H: A1.11, A3.1, C6.13
_64V: C4.13, C5.10
_128H: A1.2, A1.12, A5.1, B2.12, C3.2
_128V: C4.12, C5.11, P9.3, P9.11
_256H: A1.4, A1.10, B2.11, B3.1, B3.2, B3.12, E1.13
_256V: B6.12, B6.13, C4.11
_ATTRACT: C7.9, D4.10, D5.11, D9.4, D9.10, H8.1, H8.15
_ATTRACTn: C6.2, C7.8, E5.2, E5.3, K9.4
_BLOUP1n: E1.11, E8.9, K8.10, K8.12
_BLOUP2n: E1.3, E8.7, K8.2, K8.4
_CLOCK: A2.2, B2.2, D2.15, F1.9
_CLOCKn: D2.13, D2.14, E3.9
_COIN: C7.2, C8.3
_COINn: C5.6, C7.1
_CP1n: E8.2, F8.4
_EXPL1n: D8.11, M1.14, N3.10
_EXPL2n: D8.8, H3.5, J1.14
_FIRE1: C7.6, D8.12, E6.7, E8.6, L3.3, L3.15, P1.1, R2.13
_FIRE1n: C7.5, E5.1, E6.15
_FIRE2: C7.10, D7.7, D8.10, E8.11, E8.12, F3.3, J3.3, J3.15, P1.13
_FIRE2n: C7.11, D7.15, E5.5
_FIRECOM1: E5.13, J8.4
_FIRECOM1STAR: J8.2, J9.4
_FIRECOM2: E5.4, H9.4
_GNEn: E4.10, E5.8
_GO1n: D6.5, H8.7, M4.1, M4.15
_GO2n: D6.9, H8.9, L4.1, L4.15
_HBLANKn: B3.5, D4.4, E2.4, E2.10, E3.10, L1.9
_HCLOCK: E3.8, F2.2, H2.2, L6.2, L7.2, N2.2, P2.2, P6.2, P7.2
_HIT1: A6.14, E6.6, E7.6
_HIT1n: E4.12, E7.5, E8.5, N3.9
_HIT2: B5.14, D7.6, E7.8
_HIT2n: E4.2, E7.9, E8.10, H3.4
_HSYNC: B3.8, E3.5
_HSYNCn: B3.9, B4.2, C3.4, C4.2, D3.9
_J1C0: N7.1, N8.7
_J1C1: N7.5, N8.5
_J1C2: N6.3, N8.11
_J1C3: M7.1, N6.4, N8.9
_J1H4: P7.12, R2.4
_J1H64: P5.12, P6.12
_J1H128: P5.13, P6.11
_J1HWINDO: D2.7, D3.4, D4.5, E2.5
_J1R0: H6.3, K6.2
_J1R1: H6.2, J6.11
_J1R2: H6.6, J6.14, R6.14
_J1R3: H6.7, J6.5, K7.5, R6.2
_J1R4: F6.5, J6.2, K7.4, R5.10
_J1R4n: F6.2, F6.6, P8.1
_J1S1: A5.11, A6.1, A6.12
_J1S2: A5.14, A6.9
_J1S4: A5.5, A6.8
_J1S8: A5.2, A6.11
_J1V1: K6.11, N6.14
_J1V2: K6.14, N6.13
_J1V4: K6.5, N6.12, R2.3
_J1V64: N5.12, P5.4
_J1V128: N5.11, P5.5
_J2C0: M8.7, N7.13
_J2C1: M8.5, N7.9
_J2C2: M6.3, M8.11
_J2C3: M6.4, M7.9, M8.9
_J2H4: L7.12, R2.10
_J2HWINDO: D2.2, D3.5, E2.12, L1.10
_J2R0: J7.3, K6.3
_J2R1: J6.10, J7.2
_J2R2: J6.13, J7.6
_J2R3: J6.6, J7.7, K7.9
_J2R4: F6.9, J6.3, K7.10
_J2R4n: F6.8, F6.12, P8.12
_J2S1: A5.10, B5.1, B5.12
_J2S2: A5.13, B5.9
_J2S4: A5.6, B5.8
_J2S8: A5.3, B5.11
_J2V1: K6.10, M6.14
_J2V2: K6.13, M6.13
_J2V4: K6.6, M6.12, R2.11
_JET1: C2.6, E1.9, R2.5
_JET1n: C2.5, E2.6, F3.1
_JET2: C2.8, E1.5, R2.9
_JET2n: C2.9, E2.8, F3.11, P5.9
_L1: J5.6, K5.6, K6.9
_L2: J5.7, K5.7, K6.12
_L4: J5.4, K5.4, K6.7
_LEFT1: F7.9, J8.9
_LEFT1STAR: J8.11, J9.10
_LEFT2: F7.5, H9.10
_LOAD0n: C1.11, D1.2, H4.1, R4.11
_LOAD1n: C1.8, D1.5, F4.1
_LOAD2n: C1.6, D1.9, K4.1, R4.3
_LOAD3n: C1.3, D1.12, J4.1
_NP: C6.1, L8.2, N9.14
_Q: C8.2, D9.2, D9.12, E8.15, F8.6, F8.9
_Qn: D5.6, D5.7, F8.8
_R0: J5.3, K5.3, K6.4
_R1: J5.2, J6.9, K5.2
_R2: J5.1, J6.12, K5.1
_R3: J5.15, J6.7, K5.15
_R4: J5.14, J6.4, K5.14
_RIGHT1: F7.13, J8.12
_RIGHT1STAR: J8.14, J9.12
_RIGHT2: F7.1, H9.12
_ROM0: F4.11, H4.11, J3.4, J4.11, J5.12, K4.11, L3.4, L4.6, M4.6
_ROM1: F4.12, H4.12, J3.6, J4.12, J5.11, K4.12, L3.6, L4.5, M4.5
_ROM2: F4.13, H4.13, J3.8, J4.13, J5.10, K4.13, L3.8, L4.4, M4.4
_ROM3: F4.14, H4.14, J3.10, J4.14, J5.9, K4.14, L3.10, L4.3, M4.3
_ROM4: F4.3, H4.3, J3.16, J4.3, K4.3, K5.12, L3.16, L4.10, M4.10
_ROM5: F4.4, H4.4, J3.18, J4.4, K4.4, K5.11, L3.18, L4.11, M4.11
_ROM6: F4.5, H4.5, J3.20, J4.5, K4.5, K5.10, L3.20, L4.12, M4.12
_ROM7: F4.6, H4.6, J3.22, J4.6, K4.6, K5.9, L3.22, L4.13, M4.13
_S1C0: L3.5, N3.5
_S1C1: L3.7, N3.1
_S1C2: L1.13, L3.9
_S1C3: L3.11, N3.13
_S1C4: L3.17, M2.3
_S1C5: L3.19, M2.4
_S1C6: L3.21, R1.9
_S1C7: L3.23, M2.6
_S1H1: N1.11, N2.14
_S1H2: N1.12, N2.13
_S1H4: N1.13, N2.12
_S1V1: M1.10, M2.14
_S1V2: M1.11, M2.13
_S1V4: M1.12, M2.12
_S2C0: H3.2, J3.5
_S2C1: H3.12, J3.7
_S2C2: J3.9, K1.9
_S2C3: H3.10, J3.11
_S2C4: J2.3, J3.17
_S2C5: J2.4, J3.19
_S2C6: C2.1, J3.21
_S2C7: J2.6, J3.23
_S2H1: H1.11, H2.14
_S2H2: H1.12, H2.13
_S2H4: H1.13, H2.12
_S2V1: J1.10, J2.14
_S2V2: J1.11, J2.13
_S2V4: J1.12, J2.12
_SCORE1n: C3.11, F3.13
_SCORE2n: C3.3, F3.10
_SHELL1: E1.4, F1.3
_SHELL1n: F1.2, F3.2
_SHELL2: E1.10, F1.6
_SHELL2n: F1.7, F3.9
_SLOW1: H8.6, J8.7
_SLOW1STAR: J8.5, J9.2
_SLOW2: H8.10, H9.2
_SPFIRECOM1: J8.3, J8.6, R7.4
_SPLEFT1: J8.10, R7.13
_SPRIGHT1: J8.13, R7.10
_START: A6.2, A6.3, B5.2, B5.3, D3.15, D5.2, D5.3, H6.14, J7.14
_STARTn: D3.14, F6.1, F6.13, L6.9, L7.1, P6.9, P7.1
_VBLANKn: B6.9, E3.4, M6.7, M6.10, N6.7, N6.10
_VCLOCK: E3.6, J2.2, K2.2, L2.2, M2.2, M5.2, M6.2, N5.2, N6.2
_VDATA1n: D1.1, D1.4, D6.6, L5.6, N6.9, R4.12
_VDATA2n: D1.10, D1.13, D6.8, L5.3, M6.9, R4.2
_VRESET: E3.11, H3.1, H3.9, H3.13, K1.10, L1.12, N3.2, N3.4, N3.12, N7.2, N7.4, N7.10, N7.12
_VRESETn: B4.9, B6.1, C2.12, C4.9, E3.12, E3.13
_VSYNCn: B6.5, C8.11

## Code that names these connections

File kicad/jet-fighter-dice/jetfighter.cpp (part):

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
#define _12MHZ     "CRYSTAL", 1
#define _CLOCK     "D2", 15 
#define _CLOCKn    "D2", 14 
#define _1H        "F1", 15
#define _2H        "A2", 14 
#define _4H        "A2", 13
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#define _128H      "B2", 12
#define _256H      "B2", 11
#define _64Hn      "C2", 4
#define _HSYNCn    "B3", 9
#define _HSYNC     "B3", 8 
#define _HBLANKn   "B3", 5
#define _HBLANK    "B3", 6
#define _HCLOCK    "E3", 8
#define _1V        "D3", 10
#define _2V        "B4", 14 
#define _4V        "B4", 13
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#define _64V       "C4", 13
#define _128V      "C4", 12
#define _256V      "C4", 11
#define _VSYNCn    "B6", 5
#define _VSYNC     "B6", 6 
#define _VBLANKn   "B6", 9
#define _VBLANK    "B6", 8
#define _VCLOCK    "E3", 6
#define _VRESETn   "C2", 12
#define _VRESET    "E3", 11
#define _1F        "C8", 9
#define _2F        "P3", 12
#define _3F        "P3", 9
#define _6F        "P3", 8
#define _SCORE1n   "C3", 11
#define _SCORE2n   "C3", 3
#define _64Hxnor128H "A1", 11
#define _R4        "J6", 4
#define _R3        "J6", 7
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#define _L4        "K6", 7
#define _L2        "K6", 12
#define _L1        "K6", 9
#define _ROM0      "J5", 12 
#define _ROM1      "J5", 11 
#define _ROM2      "J5", 10
#define _ROM3      "J5", 9
#define _ROM4      "K5", 12
#define _ROM5      "K5", 11
#define _ROM6      "K5", 10
#define _ROM7      "K5", 9
#define _S1C0      "L3", 5
#define _S1C1      "L3", 7
#define _S1C2      "L3", 9
#define _S1C3      "L3", 11
#define _S1C4      "L3", 17
#define _S1C5      "L3", 19
#define _S1C6      "L3", 21
#define _S1C7      "L3", 23
#define _S2C0      "J3", 5
#define _S2C1      "J3", 7
#define _S2C2      "J3", 9
#define _S2C3      "J3", 11
#define _S2C4      "J3", 17
#define _S2C5      "J3", 19
#define _S2C6      "J3", 21
#define _S2C7      "J3", 23
#define _J1C1      "N8", 5
#define _J1C0      "N8", 7
#define _J1C3      "N8", 9
#define _J1C2      "N8", 11
#define _J2C1      "M8", 5
#define _J2C0      "M8", 7
#define _J2C3      "M8", 9
#define _J2C2      "M8", 11
#define _LOAD3n    "C1", 3
#define _LOAD2n    "C1", 6
#define _LOAD1n    "C1", 8
#define _LOAD0n    "C1", 11
#define _NP        "L8", 2

/* in the manual it says:
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
/* page 2 */

#define _J1H4      "P7", 12
#define _J1H64     "P6", 12
#define _J1H128    "P6", 11
#define _J1HWINDO  "D2", 7
#define _J1HWINDOn "D2", 6
#define _J1V1      "N6", 14
#define _J1V2      "N6", 13
#define _J1V4      "N6", 12
#define _J1V64     "N5", 12
#define _J1V128    "N5", 11
#define _VDATA1n   "L5", 6
#define _JET1n     "E2", 6
#define _JET1      "C2", 6
#define _J1S1      "A6", 12
#define _J1S2      "A6", 9
#define _J1S4      "A6", 8
#define _J1S8      "A6", 11
#define _J2H4      "L7", 12
#define _J2HWINDO  "D2", 2
#define _J2HWINDOn "D2", 3
#define _J2V1      "M6", 14
#define _J2V2      "M6", 13
#define _J2V4      "M6", 12
#define _VDATA2n   "L5", 3  //VDATA2 on diagram
#define _JET2n     "E2", 8
#define _JET2      "C2", 8
#define _J2S1      "B5", 12
#define _J2S2      "B5", 9
#define _J2S4      "B5", 8
#define _J2S8      "B5", 11
#define _HIT1      "E7", 6
#define _HIT1n     "E7", 5
#define _BLOUP2n   "E8", 7
#define _HIT2      "E7", 8
#define _HIT2n     "E7", 9
#define _BLOUP1n   "E8", 9
#define _FIRE1n    "E6", 15
#define _FIRE1     "C7", 6
#define _EXPL1n    "D8", 11
#define _EXPLO1TRIG "D6", 1
#define _FIRE2n    "D7", 15
#define _FIRE2     "C7", 10
#define _EXPL2n    "D8", 8
#define _EXPLO2TRIG "D6", 13
#define _S1H1      "N2", 14
#define _S1H2      "N2", 13
#define _S1H4      "N2", 12
#define _S1V1      "M2", 14 
#define _S1V2      "M2", 13
#define _S1V4      "M2", 12
#define _SHELL1n   "F1", 2
#define _SHELL1    "F1", 3
#define _S2H1      "H2", 14
#define _S2H2      "H2", 13
#define _S2H4      "H2", 12
#define _S2V1      "J2", 14 
#define _S2V2      "J2", 13
#define _S2V4      "J2", 12
#define _SHELL2n   "F1", 7
#define _SHELL2    "F1", 6

/* page 3 */

#define _J1R0       "H6", 3 
#define _J1R1       "H6", 2
#define _J1R2       "H6", 6
#define _J1R3       "H6", 7
#define _J1R4       "F6", 5
#define _J1R4n      "F6", 6
#define _J2R0       "J7", 3 
#define _J2R1       "J7", 2
#define _J2R2       "J7", 6
#define _J2R3       "J7", 7
#define _J2R4       "F6", 9
#define _J2R4n      "F6", 8
#define _SPLEFT1    "R7", 13 
#define _SPFIRECOM1 "R7", 4 
#define _SPRIGHT1   "R7", 10 
#define _SLOW1      "J8", 7
#define _LEFT1      "J8", 9
#define _RIGHT1     "J8", 12
#define _FIRECOM1   "J8", 4
#define _GO1n       "H8", 7 
#define _GO2n       "H8", 9
#define _1CREDIT    "D8", 6 
#define _2CREDIT    "C8", 5
#define _COIN       "C7", 2 
#define _COINn      "C5", 6
#define _START      "D3", 15
#define _STARTn     "D3", 14 
#define _1PLAY      "E8", 13
#define _Q          "F8", 6
#define _Qn         "F8", 8
#define _ATTRACTn   "C7", 8 
#define _ATTRACT    "D5", 11
#define _ENDGAMEn   "E8", 4
#define _GNEn       "E5", 8  // Game Near End (flashes score)
#define _FAST1n     "JOYSTICK1", Joystick::UP 
#define _SLOW1STAR  "J9", 2
#define _LEFT1STAR  "J9", 10
#define _RIGHT1STAR "J9", 12
#define _FIRECOM1STAR "J9", 4
#define _SLOW1      "J8", 7
#define _LEFT1      "J8", 9
#define _RIGHT1     "J8", 12
#define _FIRECOM1   "J8", 4
#define _FAST2n     "JOYSTICK2", Joystick::UP 
#define _SLOW2      "H9", 2
#define _LEFT2      "H9", 10
#define _RIGHT2     "H9", 12
#define _FIRECOM2   "H9", 4
#define _CP1n       "F8", 4
#define _CP2n       VCC // ignore coin 2 circuit


//*****circuit layout  *****
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CONNECTION("VIDEO", 1,   "D4", 3) 
CONNECTION("VIDEO", 2,   "E4", 6)  

CONNECTION("VIDEO", Video::VBLANK_PIN, _VBLANK)
CONNECTION("VIDEO", Video::HBLANK_PIN, _HBLANK) 


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CONNECTION(_128V,          "P9", 3)
CONNECTION("COIN_IN", i1,  "P9", 1)

// skipping coin 2 circuit
//CONNECTION(GND,            "F8", 11)

//CONNECTION(VCC,            "R9", 10)
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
